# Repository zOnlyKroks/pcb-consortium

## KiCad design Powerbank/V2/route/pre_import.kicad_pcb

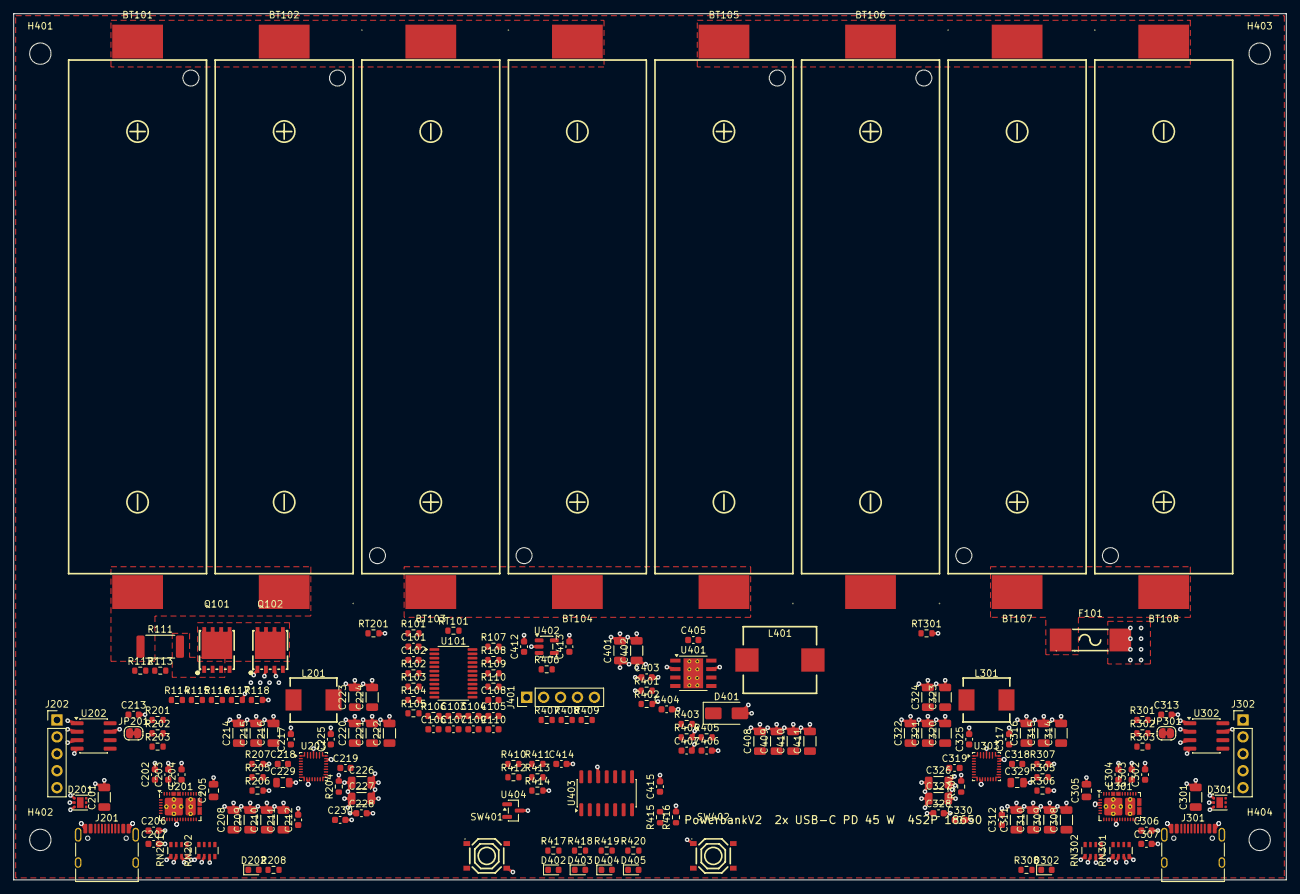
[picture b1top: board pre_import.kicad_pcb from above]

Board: 4 copper layers, 191.0 x 130.0 mm, 193 parts (0 on the bottom side), 121 nets.

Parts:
BT101, BT102, BT103, BT104, BT105, BT106, BT107, BT108: 18650; BatteryHolder_BH-18650-B1BA002
C101, C102, C412, C413: 1uF; C_0603_1608Metric
C103, C104, C105, C106, C107, C108, C109, C110, C212, C213, C217, C225, C228, C312, C313, C317, C325, C328, C405, C414, C415: 100nF; C_0603_1608Metric
C201, C208, C209, C210, C211, C214, C215, C216, C220, C221, C222, C223, C224, C226, C227, C301, C308, C309, C310, C311, C314, C315, C316, C320, C321, C322, C323, C324, C326, C327, C401, C402: 10uF 50V; C_1206_3216Metric
C202, C203, C204, C302, C303, C304: 10uF; C_0603_1608Metric
C205, C305: 22uF 25V; C_0805_2012Metric
C206, C207, C306, C307: 330pF; C_0603_1608Metric
C218, C219, C318, C319: 47nF; C_0603_1608Metric
C229, C329: 4.7uF 25V; C_0805_2012Metric
C230, C330: 1nF; C_0603_1608Metric
C403, C404: 10nF; C_0603_1608Metric
C406: 2.2nF; C_0603_1608Metric
C407: 22pF; C_0603_1608Metric
C408, C409, C410, C411: 47uF 10V; C_1206_3216Metric
D201, D301: TVS2200; WSON-6-1EP_2x2mm_P0.65mm_EP1x1.6mm
D202, D302: CHG; LED_0603_1608Metric
D401: SS54; D_SMA
D402: 1/4; LED_0603_1608Metric
D403: 2/4; LED_0603_1608Metric
D404: 3/4; LED_0603_1608Metric
D405: 4/4; LED_0603_1608Metric
F101: 20A; Fuse_10.3x3.2_1032
H401, H402, H403, H404: M3; MountingHole_3.2mm_M3
J201, J301: TYPE-C-31-M-12; USB_C_Receptacle_HRO_TYPE-C-31-M-12
J202, J302: EE_PROG; PinHeader_1x05_P2.54mm_Vertical
J401: PD_HOST; PinHeader_1x05_P2.54mm_Vertical
JP201, JP301: EE_PWR; SolderJumper-2_P1.3mm_Bridged_RoundedPad1.0x1.5mm
L201, L301: 2.2uH; L_7.0x6.6_MWSA0603S
L401: 4.7uH; L_11x10_TMPA1004S
Q101, Q102: AON6512; PDFN-8_5x6_AON6512
R101, R116, R208, R308, R411, R412: 1k; R_0603_1608Metric
R102, R103, R104, R105, R106, R112, R113, R204, R304: 100R; R_0603_1608Metric
R107, R108, R110, R203, R303, R407, R408, R409, R416: 10k; R_0603_1608Metric
R109, R406: 100k; R_0603_1608Metric
R111: 2mR; R_2512_6332Metric
R114, R410: 4.7k; R_0603_1608Metric
R115, R117: 1M; R_0603_1608Metric
R118: 470k; R_0603_1608Metric
R201, R202, R301, R302: 2.2k; R_0603_1608Metric
R205, R305: 5.23k; R_0603_1608Metric
R206, R306: 30.1k; R_0603_1608Metric
R207, R307: 27k; R_0603_1608Metric
R401: 665k; R_0603_1608Metric
R402: 130k; R_0603_1608Metric
R403: 10.5k; R_0603_1608Metric
R404: 1.96k; R_0603_1608Metric
R405: 37.4k; R_0603_1608Metric
R413: 1.5k; R_0603_1608Metric
R414: 15k; R_0603_1608Metric
R415: 51k; R_0603_1608Metric
R417, R418, R419, R420: 6.8k; R_0603_1608Metric
RN201, RN202, RN301, RN302: 4x10k; R_Array_Convex_4x0603
RT101, RT201, RT301: 10k B3380; R_0603_1608Metric
SW401: PD_RESET; SW_TS-1187A_5.1x5.1
SW402: GAUGE; SW_TS-1187A_5.1x5.1
U101: BQ7791501; TSSOP-24_4.4x7.8mm_P0.65mm
U201, U301: TPS25751DREF; Texas_REF0038A_WQFN-38-2EP_6x4mm_P0.4_Via0.3
U202, U302: CAT24C512WI; SOIC-8_3.9x4.9mm_P1.27mm
U203, U303: BQ25798RQM; Texas_RQM0029A_VQFN-29_4x4mm_P0.4mm
U401: TPS54531DDA; TI_SO-PowerPAD-8_ThermalVias
U402: ME6211C33M5G; SOT-23-5
U403: LM339; SOIC-14_3.9x8.7mm_P1.27mm
U404: TL431B; SOT-23

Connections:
+3V3: C202.1, C302.1, C413.1, J401.1, R208.1, R308.1, R407.2, R408.2, R409.2, U201.38, U301.38, U402.5
+5V: C205.1, C305.1, C408.1, C409.1, C410.1, C411.1, C412.1, L401.2, R403.1, R406.1, U201.34, U301.34, U402.1
+BATT: C226.1, C227.1, C228.1, C326.1, C327.1, C328.1, C401.1, C402.1, C403.1, F101.2, R204.2, R304.2, R401.1, SW402.1, U203.22, U203.23, U303.22, U303.23, U401.2
-BATT: BT101.2, BT102.2, C101.2, C102.2, C106.2, C107.1, C109.2, C110.2, R106.1, R109.2, R110.2, R111.1, R112.1, RT101.2, U101.9, U101.23, U101.24
/Battery/BMS_AVDD: C102.1, U101.2, U101.20
/Battery/BMS_VDD: C101.1, R101.2, R107.1, U101.1
/Battery/CHG_DRV: R116.1, U101.13
/Battery/DSG_DRV: R114.1, U101.12
/Battery/LD: R118.1, U101.14
/Battery/SRN_F: C108.2, C110.1, R113.2, U101.11
/Battery/SRP_F: C108.1, C109.1, R112.2, U101.10
/Port A/CHG_INT_A: R203.1, U201.18, U203.21
/Port A/DM_A: J201.A7, J201.B7, U201.27
/Port A/DP_A: J201.A6, J201.B6, U201.26
/Port A/I2CC_SCL_A: J202.3, R201.1, U201.17, U202.6, U203.14
/Port A/I2CC_SDA_A: J202.4, R202.1, U201.16, U202.5, U203.15
/Port A/LDO3V3_A: C203.1, J202.2, JP201.1, R201.2, R202.2, R203.2, U201.1, U201.2
/Port A/PMID_A: C214.1, C215.1, C216.1, C217.1, U203.29
/Port A/PPHV_A: C208.1, C209.1, C210.1, C211.1, C212.1, U201.20, U203.2, U203.3, U203.8, U203.9
/Port A/REGN_A: C229.1, R205.1, U203.5, U203.17
/Port A/SYS_A: C220.1, C221.1, C222.1, C223.1, C224.1, C225.1, U203.25
/Port A/VBUS_A: C201.1, D201.4, D201.5, D201.6, J201.A4, J201.A9, J201.B4, J201.B9, U201.23, U201.32
/Port B/CHG_INT_B: R303.1, U301.18, U303.21
/Port B/DM_B: J301.A7, J301.B7, U301.27
/Port B/DP_B: J301.A6, J301.B6, U301.26
/Port B/I2CC_SCL_B: J302.3, R301.1, U301.17, U302.6, U303.14
/Port B/I2CC_SDA_B: J302.4, R302.1, U301.16, U302.5, U303.15
/Port B/LDO3V3_B: C303.1, J302.2, JP301.1, R301.2, R302.2, R303.2, U301.1
/Port B/PMID_B: C314.1, C315.1, C316.1, C317.1, U303.29
/Port B/PPHV_B: C308.1, C309.1, C310.1, C311.1, C312.1, U301.20, U303.2, U303.3, U303.8, U303.9
/Port B/REGN_B: C329.1, R305.1, U303.5, U303.17
/Port B/SYS_B: C320.1, C321.1, C322.1, C323.1, C324.1, C325.1, U303.25
/Port B/VBUS_B: C301.1, D301.4, D301.5, D301.6, J301.A4, J301.A9, J301.B4, J301.B9, U301.23, U301.32
/System/COMP5: C407.1, R405.1, U401.6
/System/FB5: R403.2, R404.1, U401.5
/System/GAUGE_V: C414.1, R410.1, R415.1, R417.1, R418.1, R419.1, R420.1, SW402.4, U403.3
/System/VSENSE_G: C415.1, R415.2, R416.1, U403.4, U403.6, U403.8, U403.10
GND: C201.2, C202.2, C203.2, C204.2, C205.2, C206.2, C207.2, C208.2, C209.2, C210.2, C211.2, C212.2, C213.2, C214.2, C215.2, C216.2, C217.2, C220.2, C221.2, C222.2, C223.2, C224.2, C225.2, C226.2, C227.2, C228.2, C229.2, C230.2, C301.2, C302.2, C303.2, C304.2, C305.2, C306.2, C307.2, C308.2, C309.2, C310.2, C311.2, C312.2, C313.2, C314.2, C315.2, C316.2, C317.2, C320.2, C321.2, C322.2, C323.2, C324.2, C325.2, C326.2, C327.2, C328.2, C329.2, C330.2, C401.2, C402.2, C403.2, C404.2, C406.2, C407.2, C408.2, C409.2, C410.2, C411.2, C412.2, C413.2, C414.2, C415.2, D201.1, D201.2, D201.3, D201.7, D301.1, D301.2, D301.3, D301.7, D401.2, J201.A1, J201.A12, J201.B1, J201.B12, J201.SH, J202.5, J301.A1, J301.A12, J301.B1, J301.B12, J301.SH, J302.5, J401.5, Q102.1, Q102.2, Q102.3, R117.2, R118.2, R206.2, R207.2, R306.2, R307.2, R402.2, R404.2, R414.2, R416.2, RN201.1, RN201.2, RN201.3, RN201.4, RN202.1, RN202.2, RN202.3, RN301.1, RN301.2, RN301.3, RN301.4, RN302.1, RN302.2, RN302.3, RT201.2, RT301.2, SW401.4, U201.3, U201.11, U201.12, U201.14, U201.31, U201.39, U202.1, U202.2, U202.3, U202.4, U202.7, U203.10, U203.11, U203.13, U203.27, U301.2, U301.3, U301.11, U301.12, U301.14, U301.31, U301.39, U302.1, U302.2, U302.3, U302.4, U302.7, U303.10, U303.11, U303.13, U303.27, U401.7, U401.9, U402.2, U403.12, U404.3
unnamed: BT101.1, BT102.1, BT103.2, BT104.2, R105.1
unnamed: BT103.1, BT104.1, BT105.2, BT106.2, R104.1
unnamed: BT105.1, BT106.1, BT107.2, BT108.2, R103.1
unnamed: BT107.1, BT108.1, F101.1, R101.1, R102.1
unnamed: C406.1, R405.2
unnamed: D202.2, R208.2
unnamed: D202.1, U203.1
unnamed: D302.2, R308.2
unnamed: D302.1, U303.1
unnamed: C405.2, D401.1, L401.1, U401.8
unnamed: D402.2, R417.2
unnamed: D402.1, U403.2
unnamed: D403.2, R418.2
unnamed: D403.1, U403.1
unnamed: D404.2, R419.2
unnamed: D404.1, U403.14
unnamed: D405.2, R420.2
unnamed: D405.1, U403.13
unnamed: C206.1, J201.A5, U201.28
unnamed: C207.1, J201.B5, U201.29
unnamed: C213.1, J202.1, JP201.2, U202.8
unnamed: C306.1, J301.A5, U301.28
unnamed: C307.1, J301.B5, U301.29
unnamed: C313.1, J302.1, JP301.2, U302.8
unnamed: Q101.5, Q101.6, Q101.7, Q101.8, Q101.9, Q102.5, Q102.6, Q102.7, Q102.8, Q102.9
unnamed: Q101.4, R114.2, R115.1
unnamed: Q101.1, Q101.2, Q101.3, R111.2, R113.1, R115.2
unnamed: Q102.4, R116.2, R117.1
unnamed: RN201.8, U201.5
unnamed: RN201.7, U201.6
unnamed: RN201.6, U201.7
unnamed: RN201.5, U201.19
unnamed: RN202.8, U201.37
unnamed: RN202.7, U201.36
unnamed: RN202.6, U201.13
unnamed: RN301.8, U301.5
unnamed: RN301.7, U301.6
unnamed: RN301.6, U301.7
unnamed: RN301.5, U301.19
unnamed: RN302.8, U301.37
unnamed: RN302.7, U301.36
unnamed: RN302.6, U301.13
unnamed: R110.1, U101.16
unnamed: R109.1, U101.17
unnamed: R107.2, U101.22
unnamed: R108.2, RT101.1, U101.18
unnamed: C107.2, R106.2, U101.8
unnamed: C105.2, C106.1, R105.2, U101.7
unnamed: C104.2, C105.1, R104.2, U101.6
unnamed: C103.2, C104.1, R103.2, U101.5
unnamed: C103.1, R102.2, U101.3, U101.4
unnamed: R108.1, U101.19
unnamed: U201.15, U201.30, U201.40
unnamed: C204.1, U201.4
unnamed: R204.1, U203.18
unnamed: C218.1, U203.4
unnamed: C219.1, U203.19
unnamed: R207.1, U203.20
unnamed: C230.1, U203.24
unnamed: C218.2, L201.1, U203.28
unnamed: C219.2, L201.2, U203.26
unnamed: R205.2, R206.1, RT201.1, U203.16
unnamed: U301.15, U301.30, U301.40
unnamed: C304.1, U301.4
unnamed: R304.1, U303.18
unnamed: C318.1, U303.4
unnamed: C319.1, U303.19
unnamed: R307.1, U303.20
unnamed: C330.1, U303.24
unnamed: C318.2, L301.1, U303.28
unnamed: C319.2, L301.2, U303.26
unnamed: R305.2, R306.1, RT301.1, U303.16
unnamed: C405.1, U401.1
unnamed: R401.2, R402.1, U401.3
unnamed: C404.1, U401.4
unnamed: R406.2, SW401.1, U402.3
unnamed: R413.2, R414.1, U403.5
unnamed: R412.2, R413.1, U403.7
unnamed: R410.2, R411.1, U403.11, U404.1, U404.2
unnamed: R411.2, R412.1, U403.9
PD_IRQ: J401.4, R409.1, U201.10, U301.10
PD_SCL: J401.2, R407.1, U201.9, U301.9
PD_SDA: J401.3, R408.1, U201.8, U301.8

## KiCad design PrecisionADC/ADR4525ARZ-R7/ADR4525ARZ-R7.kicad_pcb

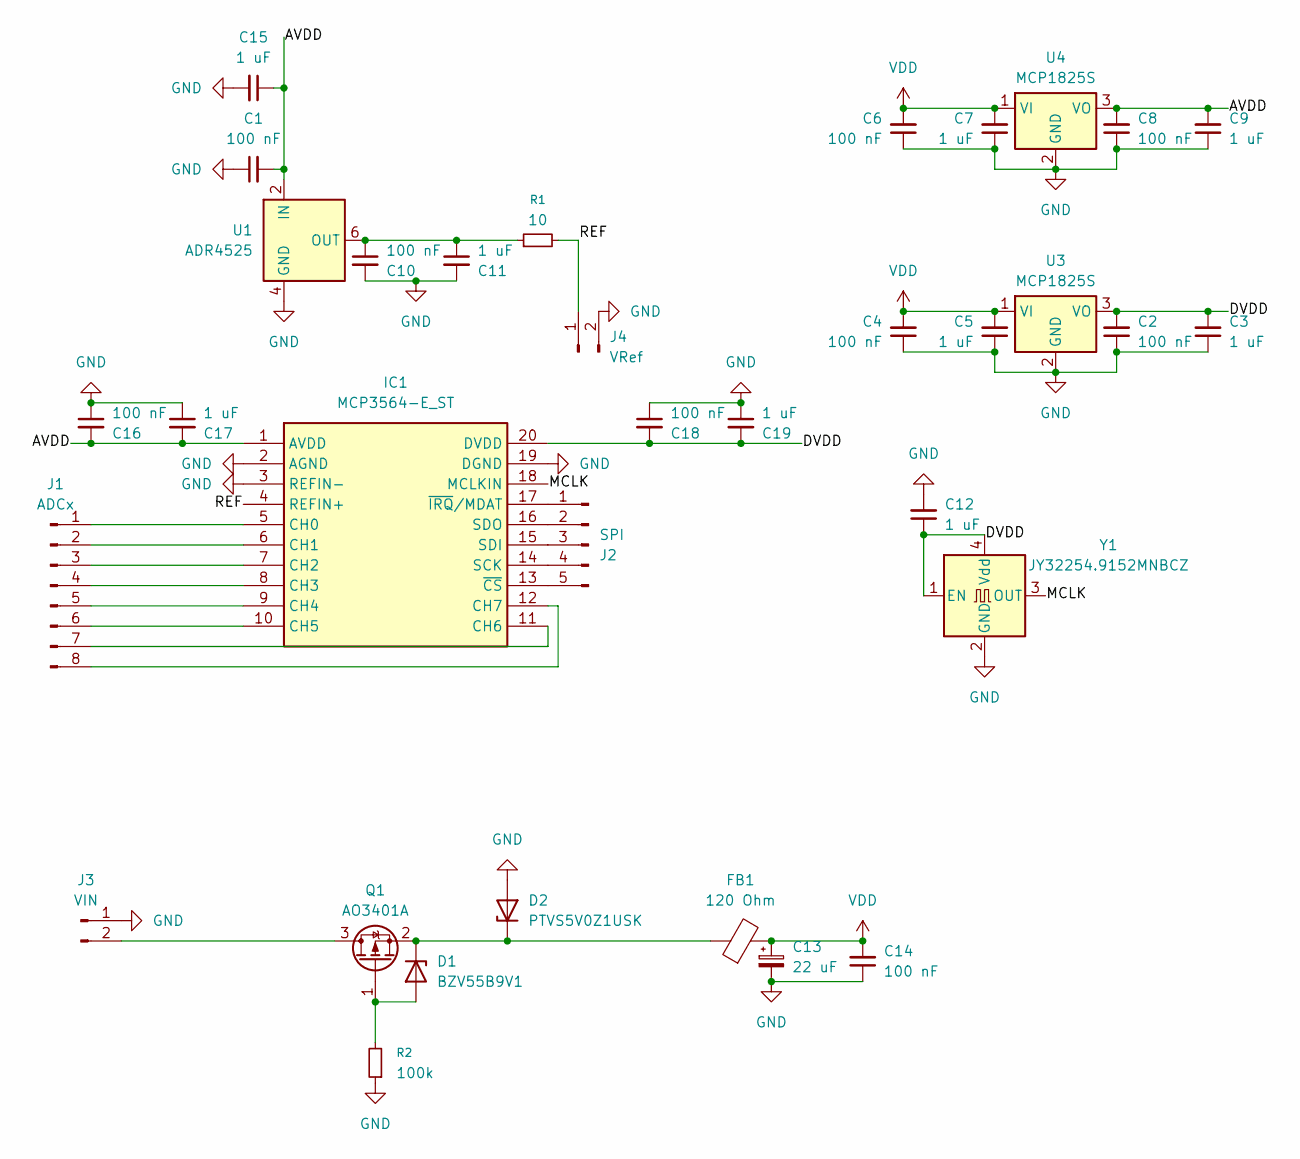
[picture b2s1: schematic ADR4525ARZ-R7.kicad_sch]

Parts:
C1, C2, C4, C6, C8, C10, C14, C16, C18: 100 nF; C_0603_1608Metric
C3, C5, C7, C9, C11, C12, C15, C17, C19: 1 uF; C_0603_1608Metric
C13: 22 uF; C_0805_2012Metric
D1: BZV55B9V1; D_MiniMELF
D2: PTVS5V0Z1USK; Nexperia_DSN1608-2_1.6x0.8mm
FB1: 120 Ohm; R_0603_1608Metric
IC1: MCP3564-E_ST; SOP65P640X120-20N; Mouser Part Number 579-MCP3564-E/ST
J1: ADCx; PinHeader_1x08_P2.54mm_Vertical
J2: SPI; PinHeader_1x05_P2.54mm_Vertical
J3: VIN; PinHeader_1x02_P2.54mm_Vertical
J4: VRef; PinHeader_1x02_P2.54mm_Vertical
Q1: AO3401A; SOT-23
R1: 10; R_0603_1608Metric
R2: 100k; R_0603_1608Metric
U1: ADR4525; SOIC-8_3.9x4.9mm_P1.27mm
U3, U4: MCP1825S; SOT-223-3_TabPin2
Y1: JY32254.9152MNBCZ; Crystal_SMD_3225-4Pin_3.2x2.5mm

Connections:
/AVDD: C1.2, C8.2, C9.2, C15.1, C16.2, C17.2, IC1.1 (AVDD), U1.2 (IN), U4.3 (VO)
/DVDD: C2.2, C3.2, C12.1, C18.2, C19.2, IC1.20 (DVDD), U3.3 (VO), Y1.1 (EN), Y1.4 (Vdd)
/MCLK: IC1.18 (MCLKIN), Y1.3 (OUT)
/REF: IC1.4 (REFIN+), J4.1, R1.2
GND: C1.1, C2.1, C3.1, C4.1, C5.1, C6.1, C7.1, C8.1, C9.1, C10.2, C11.2, C12.2, C13.2, C14.1, C15.2, C16.1, C17.1, C18.1, C19.1, D2.2 (A), IC1.2 (AGND), IC1.3 (REFIN-), IC1.19 (DGND), J3.1, J4.2, R2.1, U1.4 (GND), U3.2 (GND), U4.2 (GND), Y1.2 (GND)
unnamed: D1.2 (A), Q1.1 (G), R2.2
unnamed: D1.1 (K), D2.1 (K), FB1.1, Q1.2 (S)
unnamed: IC1.5 (CH0), J1.1
unnamed: IC1.6 (CH1), J1.2
unnamed: IC1.7 (CH2), J1.3
unnamed: IC1.8 (CH3), J1.4
unnamed: IC1.9 (CH4), J1.5
unnamed: IC1.10 (CH5), J1.6
unnamed: IC1.11 (CH6), J1.7
unnamed: IC1.12 (CH7), J1.8
unnamed: IC1.14 (SCK), J2.4
unnamed: IC1.15 (SDI), J2.3
unnamed: IC1.16 (SDO), J2.2
unnamed: IC1.13 (~CS), J2.5
unnamed: IC1.17 (~IRQ/MDAT), J2.1
unnamed: J3.2, Q1.3 (D)
unnamed: C10.1, C11.1, R1.1, U1.6 (OUT)
VDD: C4.2, C5.2, C6.2, C7.2, C13.1, C14.2, FB1.2, U3.1 (VI), U4.1 (VI)

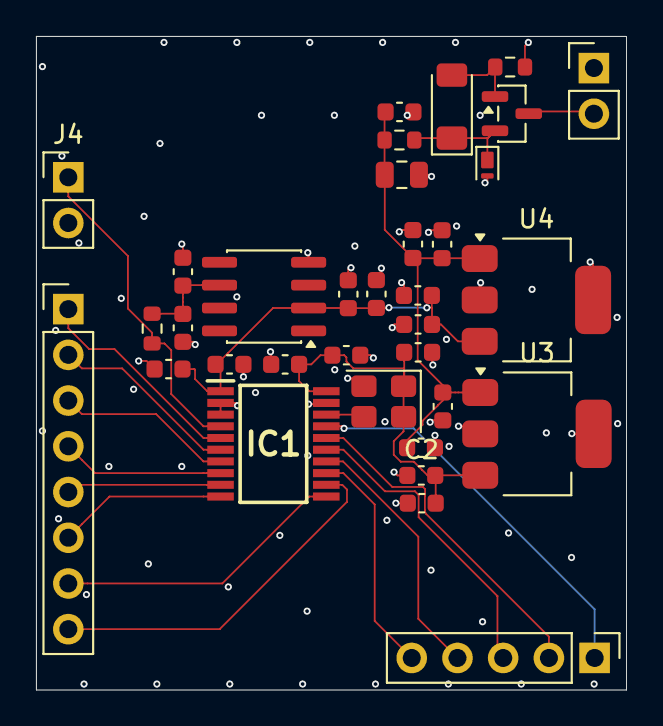
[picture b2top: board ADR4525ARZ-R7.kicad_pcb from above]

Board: 4 copper layers, 32.8 x 36.3 mm, 34 parts (0 on the bottom side), 23 nets.

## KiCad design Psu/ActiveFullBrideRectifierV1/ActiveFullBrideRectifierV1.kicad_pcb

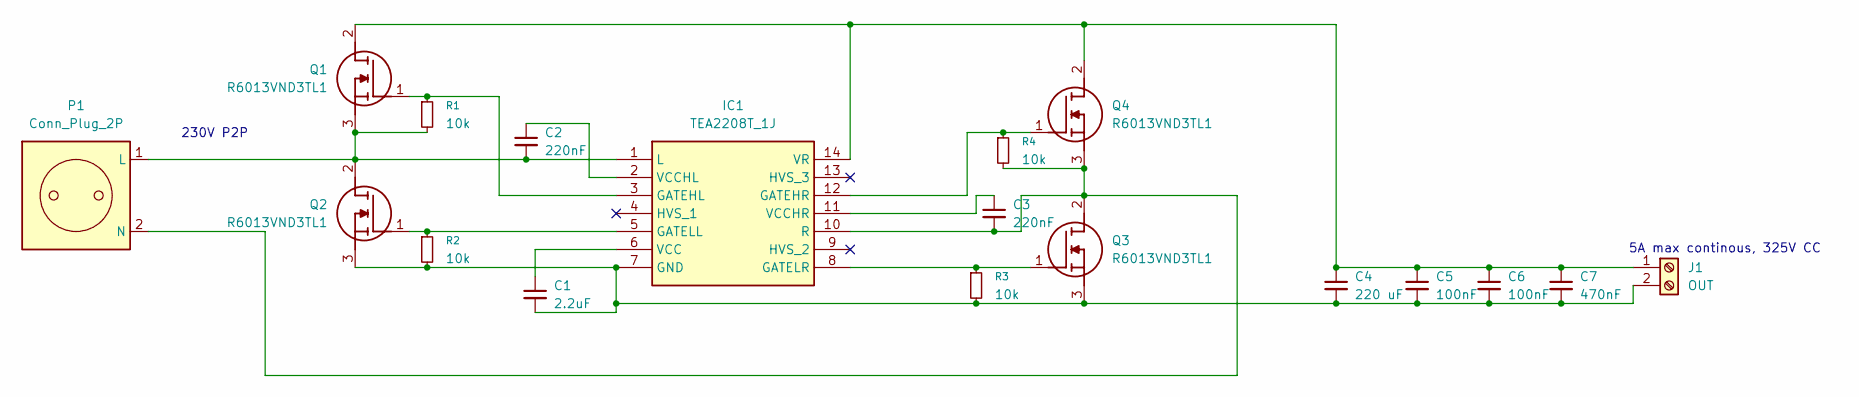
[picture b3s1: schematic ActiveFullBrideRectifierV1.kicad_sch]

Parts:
C1: 2.2uF; C_2220_5750Metric; LCSC Part # C153032
C2, C3: 220nF; C_1812_4532Metric; LCSC Part # C146179
C4: 220 uF; CP_Radial_D30.0mm_P10.00mm_SnapIn; LCSC Part # C350245
C5, C6: 100nF; C_1812_4532Metric; LCSC Part # C696256
C7: 470nF; C_2220_5750Metric; LCSC Part # C2987945
IC1: TEA2208T_1J; Mouser Part Number 771-TEA2208T/1J
J1: OUT; TerminalBlock_Phoenix_MKDS-1,5-2_1x02_P5.00mm_Horizontal
P1: Conn_Plug_2P; TerminalBlock_Phoenix_MKDS-1,5-2_1x02_P5.00mm_Horizontal
Q1, Q2, Q3, Q4: R6013VND3TL1; Mouser Part Number 755-R6013VND3TL1
R1, R2, R3, R4: 10k; R_2010_5025Metric; LCSC Part # C2078100

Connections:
unnamed: IC1.3 (GATEHL), Q1.1 (G), R1.1
unnamed: IC1.12 (GATEHR), Q4.1 (G), R4.1
unnamed: IC1.5 (GATELL), Q2.1 (G), R2.1
unnamed: IC1.8 (GATELR), Q3.1 (G), R3.1
unnamed: C1.2, C4.2, C5.2, C6.2, C7.2, IC1.7 (GND), J1.2, Q2.3 (S), Q3.3 (S), R2.2, R3.2
unnamed: C2.2, IC1.1 (L), P1.1 (L), Q1.3 (S), Q2.2 (D), R1.2
unnamed: C3.2, IC1.10 (R), P1.2 (N), Q3.2 (D), Q4.3 (S), R4.2
unnamed: C1.1, IC1.6 (VCC)
unnamed: C2.1, IC1.2 (VCCHL)
unnamed: C3.1, IC1.11 (VCCHR)
unnamed: C4.1, C5.1, C6.1, C7.1, IC1.14 (VR), J1.1, Q1.2 (D), Q4.2 (D)

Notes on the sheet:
5A max continous, 325V CC
230V P2P

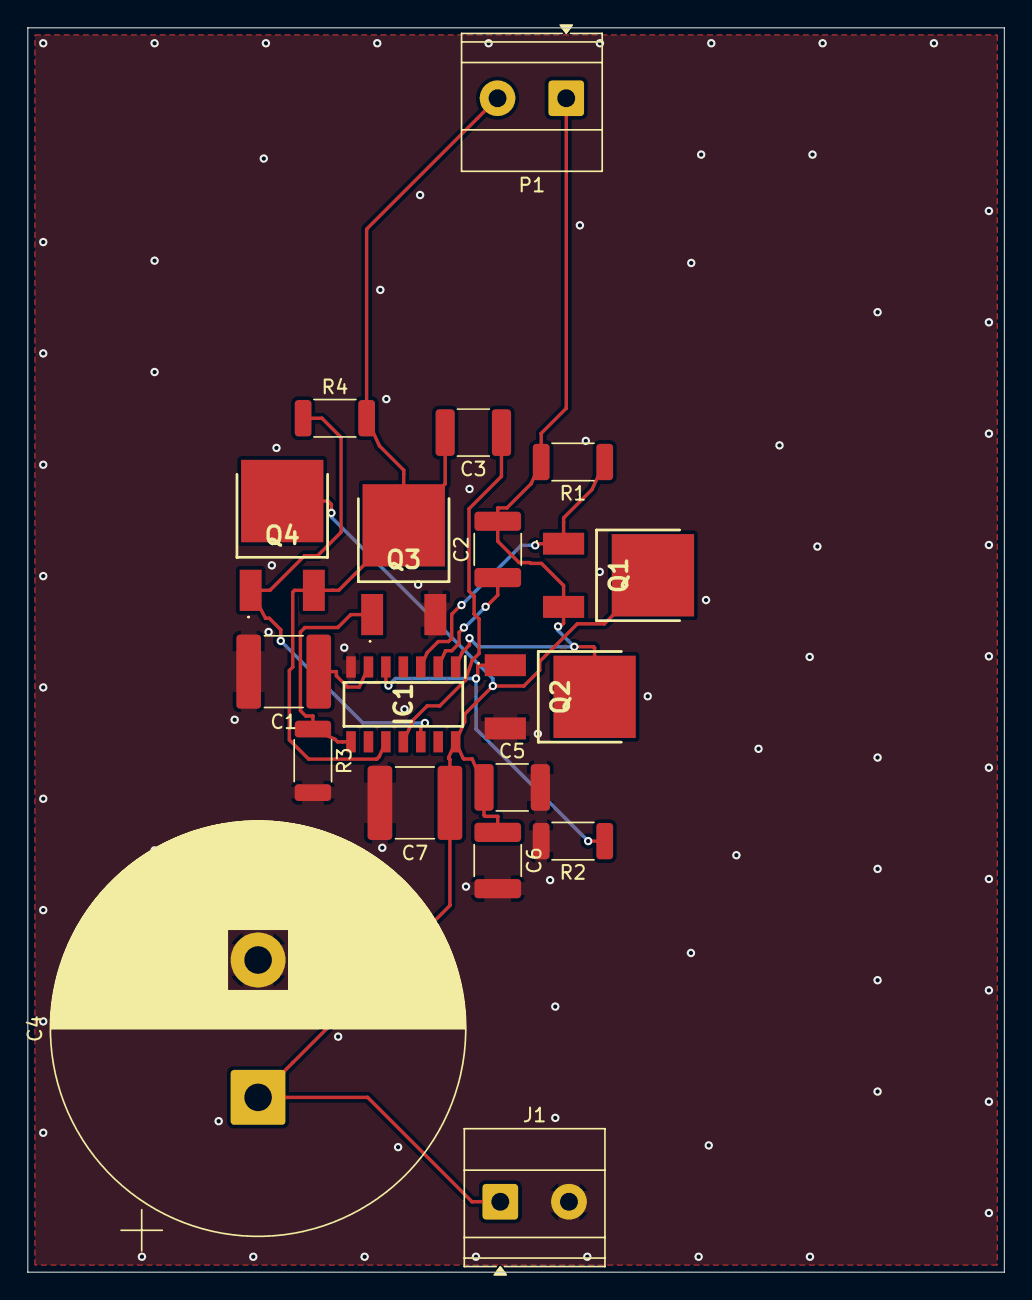
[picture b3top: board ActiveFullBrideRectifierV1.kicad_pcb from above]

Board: 2 copper layers, 71.1 x 90.6 mm, 18 parts (0 on the bottom side), 11 nets.

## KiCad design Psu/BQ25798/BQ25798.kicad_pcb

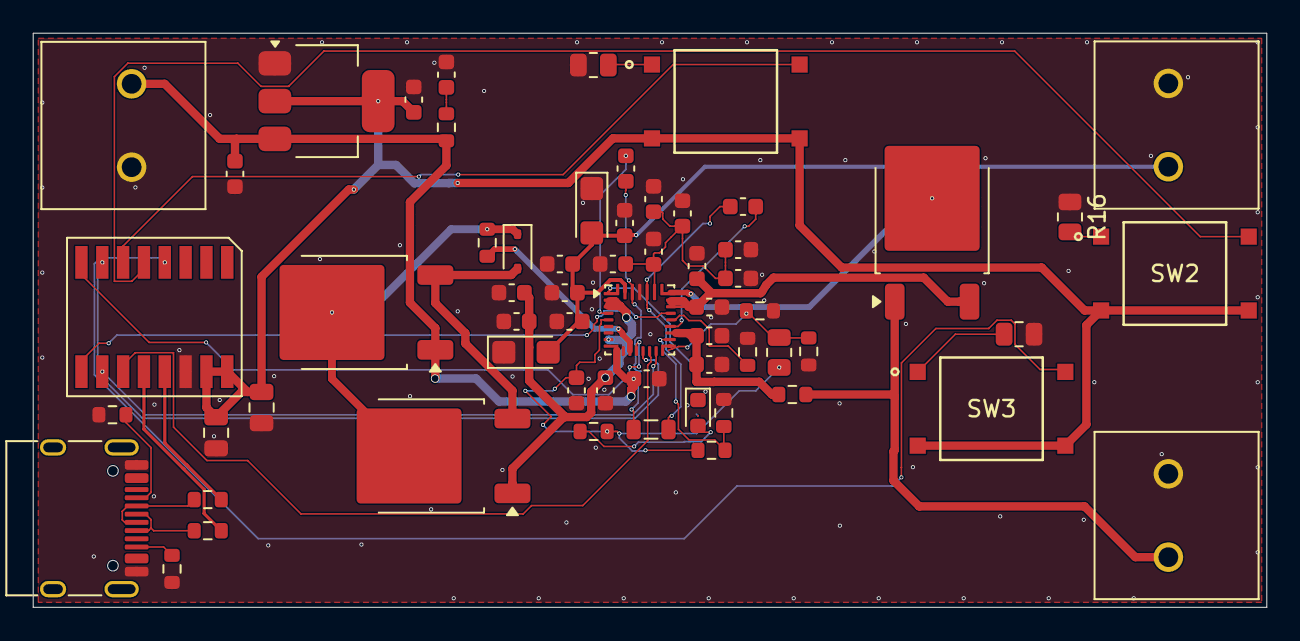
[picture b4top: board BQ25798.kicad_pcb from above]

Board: 2 copper layers, 75.2 x 35.0 mm, 61 parts (0 on the bottom side), 41 nets.

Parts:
C1: 2.2 uF; C_0603_1608Metric
C2, C6, C12, C18: 0.1 uF; C_0603_1608Metric
C3, C4, C23, C24: 47 nF; C_0603_1608Metric
C5: 4.7 uF; C_0603_1608Metric
C7, C8, C9, C10, C11, C13, C14, C15, C19, C20, C21, C22, C25, C26: 10 uF; C_0603_1608Metric
C16, C17: 33 uF; CP_EIA-3216-18_Kemet-A
C27, C28: 100nF; C_0805_2012Metric
D1: LED; LED_0603_1608Metric
D2: BZX384-B12,115; D_SOD-323
J2: IN; WJ500V-5.08-2P
J3: UPS; WJ500V-5.08-2P
J5: BAT; WJ500V-5.08-2P
J6: USB_C_Receptacle_USB2.0; USB_C_Receptacle_HRO_TYPE-C-31-M-12
L1: 1 uH; L_0805_2012Metric
Q1, Q2, Q3: NMOS; TO-252-2
R1: 2.2k; R_0603_1608Metric
R2: 2; R_0603_1608Metric
R3: 127k; R_0603_1608Metric
R4: 100k; R_0603_1608Metric
R5: 6.04k; R_0603_1608Metric
R6: 294; R_0603_1608Metric
R7: 100; R_0603_1608Metric
R8: 5.2k; R_0805_2012Metric
R9: 30.31k; R_0603_1608Metric
R10, R11: 5.1k; R_0603_1608Metric
R12, R15, R16: 10k Ohm; R_0805_2012Metric
R13, R14: 22; R_0603_1608Metric
SW1, SW2, SW3: KH-6X6X5H-STM; KH-6X6X5H-STM_SKE
TH1: 10k; R_0603_1608Metric
U1: BQ25798; Texas_RQM0029A_VQFN-29_4x4mm_P0.4mm
U2: CH552G
U3: AMS1117-3.3; SOT-223-3_TabPin2

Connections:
+3V3: C26.1, C27.2, C28.2, SW1.C, SW1.D, SW2.C, SW2.D, SW3.C, SW3.D, U2.15 (VCC), U2.16 (3V3), U3.2 (VO)
/REGN: C5.1, R1.2, R3.2, R8.2, U1.5 (REGN)
/VIN: C2.1, C25.1, J2.1, Q1.1 (D), R2.1, U1.9 (VAC1), U3.3 (VI)
D+: R14.2, U2.12 (P3.6)
D-: R13.2, U2.13 (P3.7)
GND: C1.1, C2.2, C5.2, C6.2, C7.2, C8.2, C9.2, C10.2, C11.2, C12.1, C13.1, C14.1, C15.1, C16.1, C17.1, C18.1, C19.1, C20.1, C21.2, C22.2, C23.2, C24.2, C25.2, C26.2, C27.1, C28.1, J2.2, J3.2, J5.2, J6.A1 (GND), J6.A12 (GND), J6.B1 (GND), J6.B12 (GND), R4.1, R5.1, R9.1, R10.1, R11.2, R12.1, R15.1, R16.1, TH1.2, U1.10 (ACDRV2), U1.27 (GND), U2.14 (GND), U3.1 (GND)
unnamed: C1.2, R2.2
unnamed: D1.2 (A), R1.1
unnamed: D1.1 (K), U1.1 (STAT)
unnamed: D2.2 (A), Q1.3 (S), Q2.3 (S)
unnamed: D2.1 (K), Q1.2 (G), Q2.2 (G), R6.1
unnamed: C12.2, C13.2, C14.2, C15.2, C16.2, C17.2, J3.1, U1.29 (PMID)
unnamed: J5.1, Q3.1 (D), R7.2
unnamed: J6.A5 (CC1), R10.2
unnamed: J6.B5 (CC2), R11.1
unnamed: J6.A6 (D+), J6.B6 (D+), R14.1
unnamed: J6.A7 (D-), J6.B7 (D-), R13.1
unnamed: C18.2, C19.2, C20.2, Q2.1 (D), U1.2 (VBUS), U1.3 (VBUS), U1.8 (VAC2)
unnamed: Q3.2 (G), U1.24 (SDRV)
unnamed: C21.1, C22.1, Q3.3 (S), U1.22 (BAT), U1.23 (BAT)
unnamed: R12.2, SW1.A
unnamed: R15.2, SW3.A
unnamed: R16.2, SW2.A
unnamed: R6.2, U1.11 (ACDRV1)
unnamed: C23.1, C24.1, R7.1, U1.18 (BATP)
unnamed: C3.1, U1.4 (BTST1)
unnamed: C4.2, U1.19 (BTST2)
unnamed: R3.1, R4.2, U1.17 (ILIM_HIZ)
unnamed: R5.2, U1.20 (PROG)
unnamed: U1.14 (SCL), U2.11 (P3.4)
unnamed: U1.15 (SDA), U2.10 (P3.3)
unnamed: C3.2, L1.1, U1.28 (SW1)
unnamed: C4.1, L1.2, U1.26 (SW2)
unnamed: C6.1, C7.1, C8.1, C9.1, C10.1, C11.1, U1.25 (SYS)
unnamed: R8.1, R9.2, TH1.1, U1.16 (TS)
unnamed: U1.13 (~CE), U2.7 (P3.1)
unnamed: U1.21 (~INT), U2.9 (P1.1)
unnamed: U1.12 (~QON), U2.8 (P3.0)
unnamed: SW3.B, U2.4 (P1.6)
unnamed: SW2.B, U2.5 (P1.7)
unnamed: SW1.B, U2.6 (RST)
